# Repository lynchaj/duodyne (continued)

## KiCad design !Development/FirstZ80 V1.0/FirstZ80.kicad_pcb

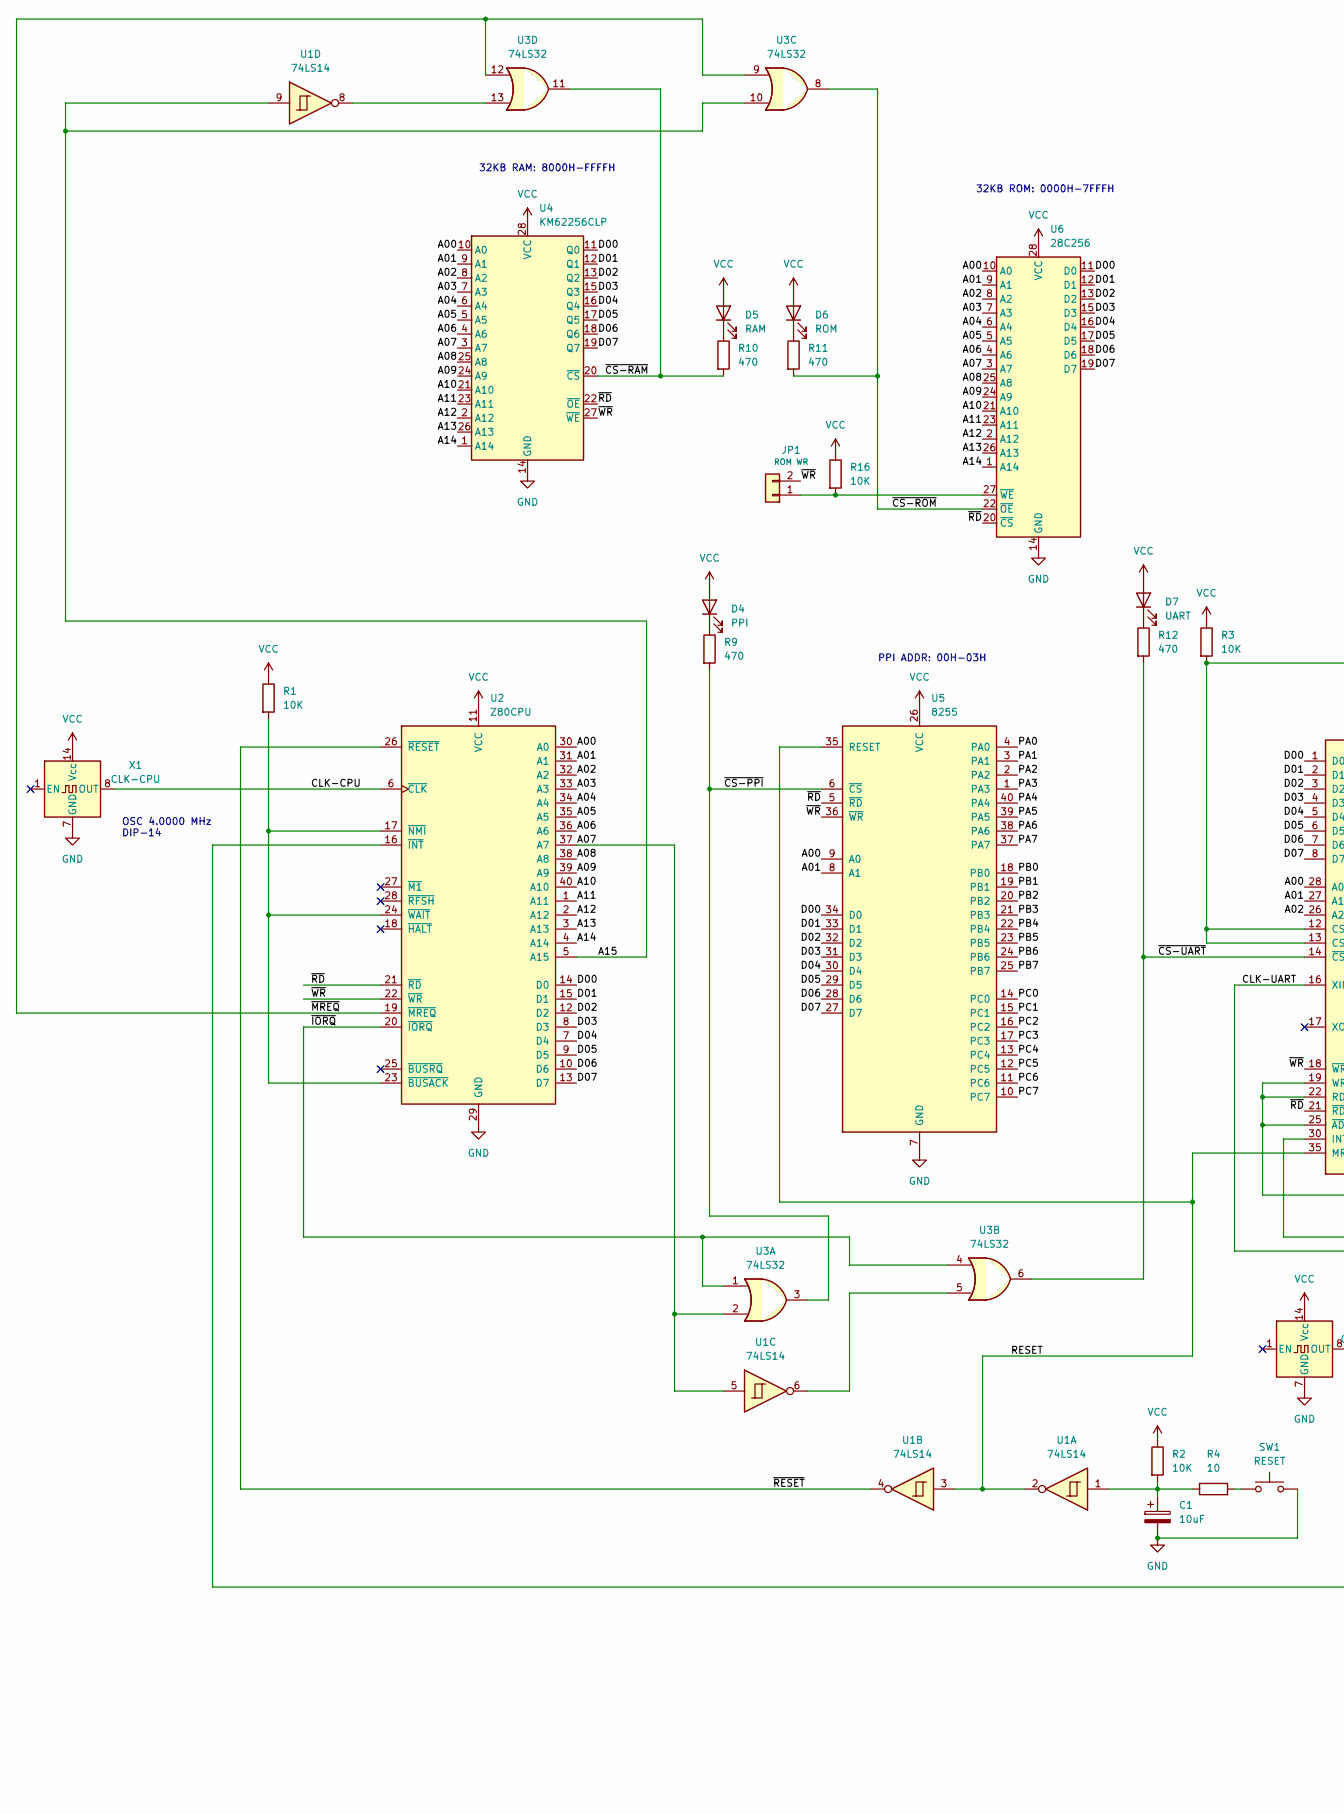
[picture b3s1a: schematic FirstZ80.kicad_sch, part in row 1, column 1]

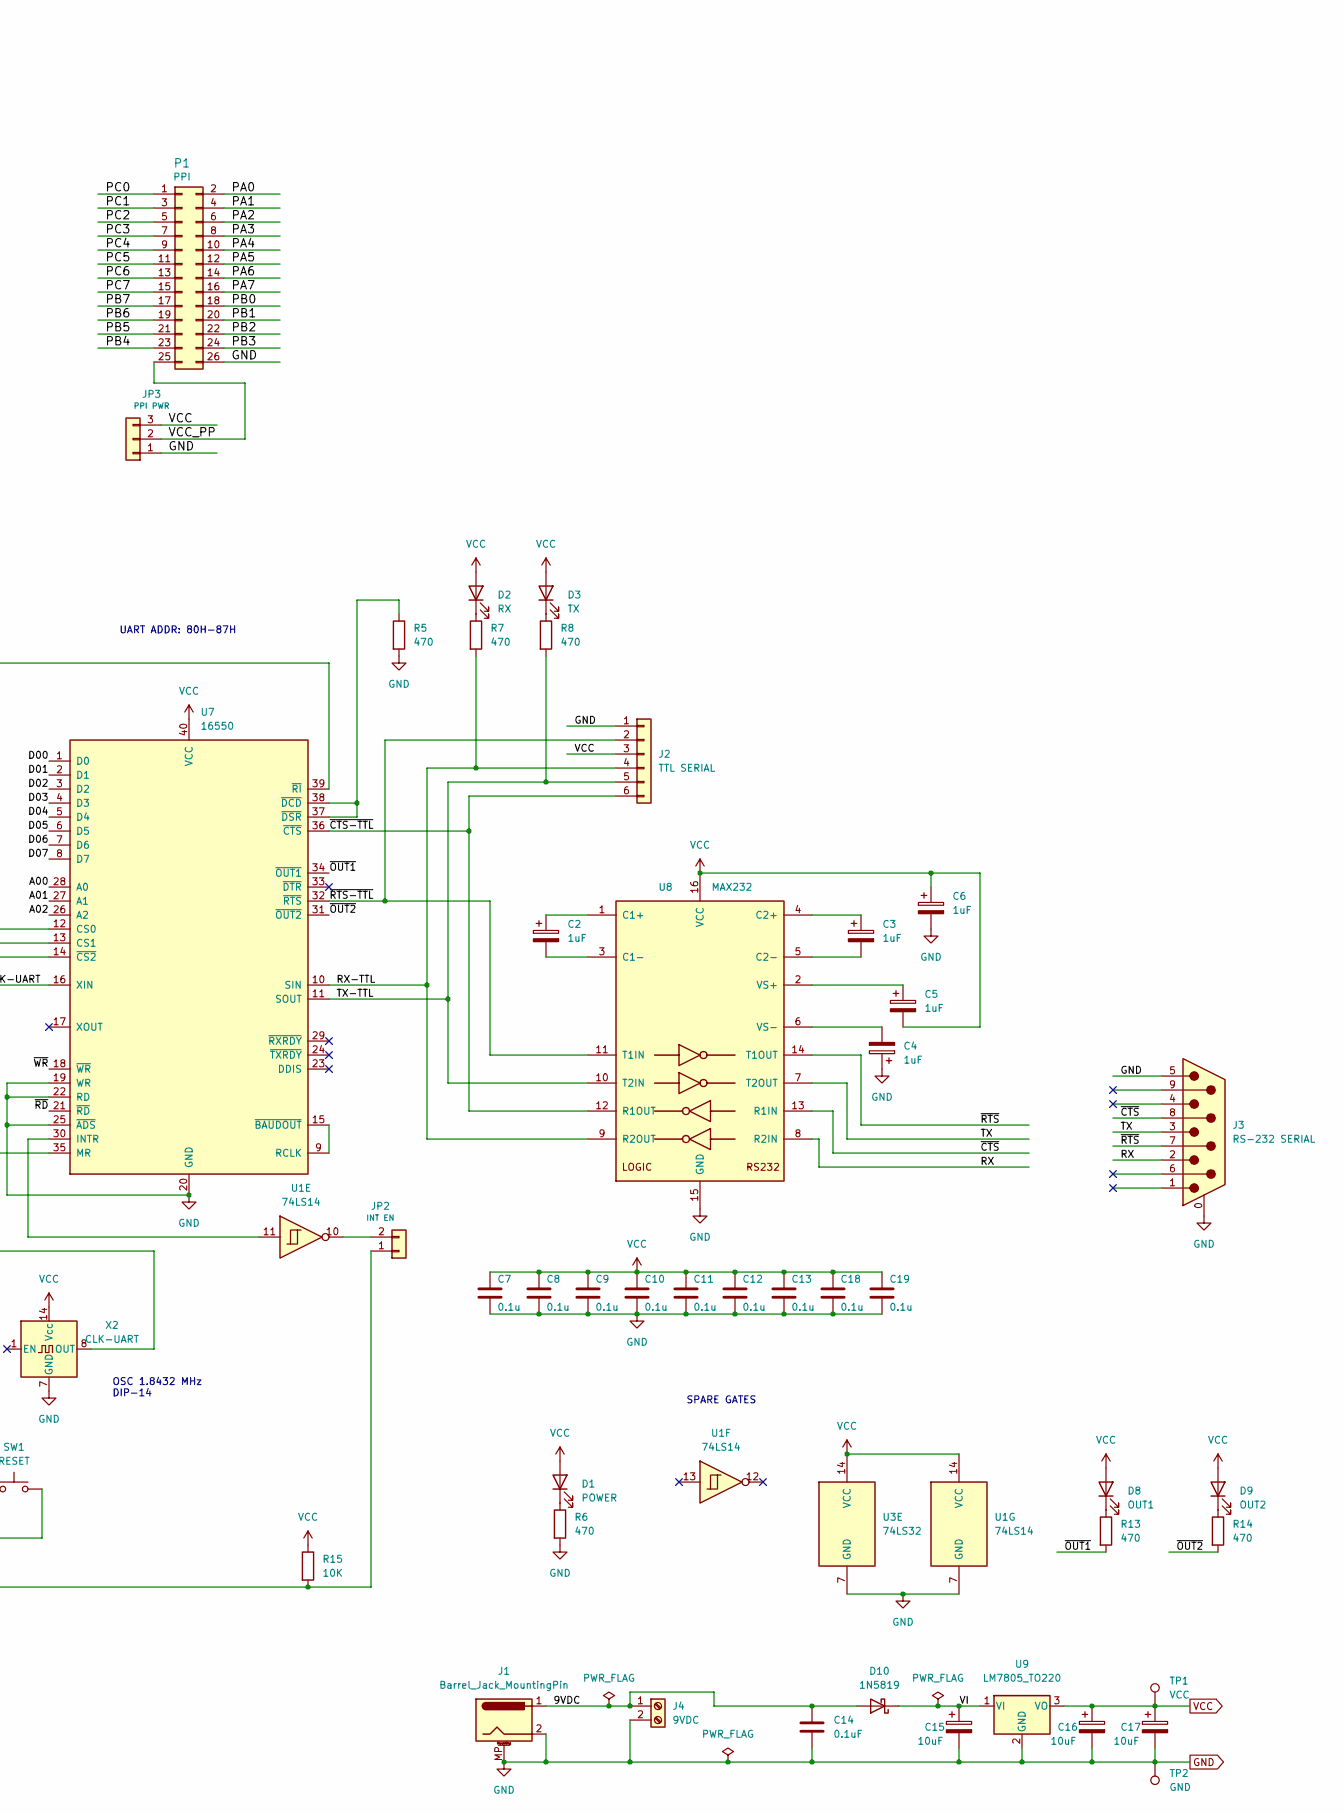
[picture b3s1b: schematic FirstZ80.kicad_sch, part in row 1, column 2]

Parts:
C1, C15, C16, C17: 10uF; CP_Radial_D5.0mm_P2.50mm
C2, C3, C4, C5, C6: 1uF; CP_Radial_D5.0mm_P2.50mm
C7, C8, C9, C10, C11, C12, C13, C18, C19: 0.1u; C_Disc_D5.0mm_W2.5mm_P5.00mm
C14: 0.1uF; C_Disc_D5.0mm_W2.5mm_P5.00mm
D1: POWER; LED_D3.0mm
D2: RX; LED_D3.0mm
D3: TX; LED_D3.0mm
D4: PPI; LED_D3.0mm
D5: RAM; LED_D3.0mm
D6: ROM; LED_D3.0mm
D7: UART; LED_D3.0mm
D8: OUT1; LED_D3.0mm
D9: OUT2; LED_D3.0mm
D10: 1N5819; D_DO-41_SOD81_P10.16mm_Horizontal
J1: Barrel_Jack_MountingPin; BarrelJack_Horizontal
J2: TTL SERIAL; PinHeader_1x06_P2.54mm_Horizontal
J3: RS-232 SERIAL; DSUB-9_Male_Horizontal_P2.77x2.84mm_EdgePinOffset4.94mm_Hou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
J4: 9VDC; TerminalBlock_Phoenix_MKDS-1,5-2-5.08_1x02_P5.08mm_Horizont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
JP1: ROM WR; PinHeader_1x02_P2.54mm_Vertical
JP2: INT EN; PinHeader_1x02_P2.54mm_Vertical
JP3: PPI PWR; PinHeader_1x03_P2.54mm_Vertical
P1: PPI; IDC-Header_2x13_P2.54mm_Horizontal
R1, R2, R3, R15, R16: 10K; R_Axial_DIN0207_L6.3mm_D2.5mm_P7.62mm_Horizontal
R4: 10; R_Axial_DIN0207_L6.3mm_D2.5mm_P7.62mm_Horizontal
R5, R6, R7, R8, R9, R10, R11, R12, R13, R14: 470; R_Axial_DIN0207_L6.3mm_D2.5mm_P7.62mm_Horizontal
SW1: RESET; SW_PUSH_6mm
TP1: VCC; PinHeader_1x01_P2.54mm_Vertical
TP2: GND; PinHeader_1x01_P2.54mm_Vertical
U1: 74LS14; DIP-14_W7.62mm_Socket_LongPads
U2: Z80CPU; DIP-40_W15.24mm_Socket_LongPads
U3: 74LS32; DIP-14_W7.62mm_Socket_LongPads
U4: KM62256CLP; DIP-28_W15.24mm_Socket_LongPads
U5: 8255; DIP-40_W15.24mm_Socket_LongPads
U6: 28C256; DIP_Socket-28_W11.9_W12.7_W15.24_W17.78_W18.5_3M_228-1277-0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
U7: 16550; DIP-40_W15.24mm_Socket_LongPads
U8: MAX232; DIP-16_W7.62mm_Socket_LongPads
U9: LM7805_TO220; TO-220-3_Horizontal_TabDown
X1: CLK-CPU; Oscillator_DIP-14
X2: CLK-UART; Oscillator_DIP-14

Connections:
/9VDC: C14.1, D10.2 (A), J1.1, J4.1
/A00: U2.30 (A0), U4.10 (A0), U5.9 (A0), U6.10 (A0), U7.28 (A0)
/A01: U2.31 (A1), U4.9 (A1), U5.8 (A1), U6.9 (A1), U7.27 (A1)
/A02: U2.32 (A2), U4.8 (A2), U6.8 (A2), U7.26 (A2)
/A03: U2.33 (A3), U4.7 (A3), U6.7 (A3)
/A04: U2.34 (A4), U4.6 (A4), U6.6 (A4)
/A05: U2.35 (A5), U4.5 (A5), U6.5 (A5)
/A06: U2.36 (A6), U4.4 (A6), U6.4 (A6)
/A07: U1.5, U2.37 (A7), U3.2, U4.3 (A7), U6.3 (A7)
/A08: U2.38 (A8), U4.25 (A8), U6.25 (A8)
/A09: U2.39 (A9), U4.24 (A9), U6.24 (A9)
/A10: U2.40 (A10), U4.21 (A10), U6.21 (A10)
/A11: U2.1 (A11), U4.23 (A11), U6.23 (A11)
/A12: U2.2 (A12), U4.2 (A12), U6.2 (A12)
/A13: U2.3 (A13), U4.26 (A13), U6.26 (A13)
/A14: U2.4 (A14), U4.1 (A14), U6.1 (A14)
/A15: U1.9, U2.5 (A15), U3.10
/CLK-CPU: U2.6 (~CLK), X1.8 (OUT)
/CLK-UART: U7.16 (XIN), X2.8 (OUT)
/D00: U2.14 (D0), U4.11 (Q0), U5.34 (D0), U6.11 (D0), U7.1 (D0)
/D01: U2.15 (D1), U4.12 (Q1), U5.33 (D1), U6.12 (D1), U7.2 (D1)
/D02: U2.12 (D2), U4.13 (Q2), U5.32 (D2), U6.13 (D2), U7.3 (D2)
/D03: U2.8 (D3), U4.15 (Q3), U5.31 (D3), U6.15 (D3), U7.4 (D3)
/D04: U2.7 (D4), U4.16 (Q4), U5.30 (D4), U6.16 (D4), U7.5 (D4)
/D05: U2.9 (D5), U4.17 (Q5), U5.29 (D5), U6.17 (D5), U7.6 (D5)
/D06: U2.10 (D6), U4.18 (Q6), U5.28 (D6), U6.18 (D6), U7.7 (D6)
/D07: U2.13 (D7), U4.19 (Q7), U5.27 (D7), U6.19 (D7), U7.8 (D7)
/PA0: P1.2, U5.4 (PA0)
/PA1: P1.4, U5.3 (PA1)
/PA2: P1.6, U5.2 (PA2)
/PA3: P1.8, U5.1 (PA3)
/PA4: P1.10, U5.40 (PA4)
/PA5: P1.12, U5.39 (PA5)
/PA6: P1.14, U5.38 (PA6)
/PA7: P1.16, U5.37 (PA7)
/PB0: P1.18, U5.18 (PB0)
/PB1: P1.20, U5.19 (PB1)
/PB2: P1.22, U5.20 (PB2)
/PB3: P1.24, U5.21 (PB3)
/PB4: P1.23, U5.22 (PB4)
/PB5: P1.21, U5.23 (PB5)
/PB6: P1.19, U5.24 (PB6)
/PB7: P1.17, U5.25 (PB7)
/PC0: P1.1, U5.14 (PC0)
/PC1: P1.3, U5.15 (PC1)
/PC2: P1.5, U5.16 (PC2)
/PC3: P1.7, U5.17 (PC3)
/PC4: P1.9, U5.13 (PC4)
/PC5: P1.11, U5.12 (PC5)
/PC6: P1.13, U5.11 (PC6)
/PC7: P1.15, U5.10 (PC7)
/RESET: U1.2, U1.3, U5.35 (RESET), U7.35 (MR)
/RX: J3.2, U8.8 (R2IN)
/RX-TTL: J2.4, R7.2, U7.10 (SIN), U8.9 (R2OUT)
/TX: J3.3, U8.7 (T2OUT)
/TX-TTL: J2.5, R8.2, U7.11 (SOUT), U8.10 (T2IN)
/VCC_PP: JP3.2, P1.25
/VI: C15.1, D10.1 (K), U9.1 (VI)
/~CS-PPI: R9.2, U3.3, U5.6 (~CS)
/~CS-RAM: R10.2, U3.11, U4.20 (~CS)
/~CS-ROM: R11.2, U3.8, U6.22 (~OE)
/~CS-UART: R12.2, U3.6, U7.14 (~CS2)
/~CTS-TTL: J2.6, U7.36 (~CTS), U8.12 (R1OUT)
/~CTS: J3.8, U8.13 (R1IN)
/~IORQ: U2.20 (~IORQ), U3.1, U3.4
/~MREQ: U2.19 (~MREQ), U3.9, U3.12
/~OUT1: R13.2, U7.34 (~OUT1)
/~OUT2: R14.2, U7.31 (~OUT2)
/~RD: U2.21 (~RD), U4.22 (~OE), U5.5 (~RD), U6.20 (~CS), U7.21 (~RD)
/~RESET: U1.4, U2.26 (~RESET)
/~RTS-TTL: J2.2, U7.32 (~RTS), U8.11 (T1IN)
/~RTS: J3.7, U8.14 (T1OUT)
/~WR: JP1.2, U2.22 (~WR), U4.27 (~WE), U5.36 (~WR), U7.18 (~WR)
GND: C1.2, C4.1, C6.2, C7.2, C8.2, C9.2, C10.2, C11.2, C12.2, C13.2, C14.2, C15.2, C16.2, C17.2, C18.2, C19.2, J1.2, J1.MP (MountPin), J2.1, J3.0 (PAD), J3.5, J4.2, JP3.1, P1.26, R5.2, R6.2, SW1.2, TP2.1, U1.7 (GND), U2.29 (GND), U3.7 (GND), U4.14 (GND), U5.7 (GND), U6.14 (GND), U7.19 (WR), U7.20 (GND), U7.22 (RD), U7.25 (~ADS), U8.15 (GND), U9.2 (GND), X1.7 (GND), X2.7 (GND)
unnamed: C1.1, R2.2, R4.1, U1.1
unnamed: C2.1, U8.1 (C1+)
unnamed: C2.2, U8.3 (C1-)
unnamed: C3.1, U8.4 (C2+)
unnamed: C3.2, U8.5 (C2-)
unnamed: C4.2, U8.6 (VS-)
unnamed: C5.1, U8.2 (VS+)
unnamed: D1.1 (K), R6.1
unnamed: D2.1 (K), R7.1
unnamed: D3.1 (K), R8.1
unnamed: D4.1 (K), R9.1
unnamed: D5.1 (K), R10.1
unnamed: D6.1 (K), R11.1
unnamed: D7.1 (K), R12.1
unnamed: D8.1 (K), R13.1
unnamed: D9.1 (K), R14.1
unnamed: JP1.1, R16.2, U6.27 (~WE)
unnamed: JP2.1, R15.2, U2.16 (~INT)
unnamed: JP2.2, U1.10
unnamed: R1.2, U2.17 (~NMI), U2.23 (~BUSACK), U2.24 (~WAIT)
unnamed: R3.2, U7.12 (CS0), U7.13 (CS1), U7.39 (~RI)
unnamed: R4.2, SW1.1
unnamed: R5.1, U7.37 (~DSR), U7.38 (~DCD)
unnamed: U1.6, U3.5
unnamed: U1.8, U3.13
unnamed: U1.11, U7.30 (INTR)
unnamed: U7.9 (RCLK), U7.15 (~BAUDOUT)
VCC: C5.2, C6.1, C7.1, C8.1, C9.1, C10.1, C11.1, C12.1, C13.1, C16.1, C17.1, C18.1, C19.1, D1.2 (A), D2.2 (A), D3.2 (A), D4.2 (A), D5.2 (A), D6.2 (A), D7.2 (A), D8.2 (A), D9.2 (A), J2.3, JP3.3, R1.1, R2.1, R3.1, R15.1, R16.1, TP1.1, U1.14 (VCC), U2.11 (VCC), U3.14 (VCC), U4.28 (VCC), U5.26 (VCC), U6.28 (VCC), U7.40 (VCC), U8.16 (VCC), U9.3 (VO), X1.14 (Vcc), X2.14 (Vcc)

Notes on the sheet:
UART ADDR: 80H-87H
SPARE GATES
PPI ADDR: 00H-03H
OSC 1.8432 MHz DIP-14
32KB ROM: 0000H-7FFFH
32KB RAM: 8000H-FFFFH
OSC 4.0000 MHz DIP-14

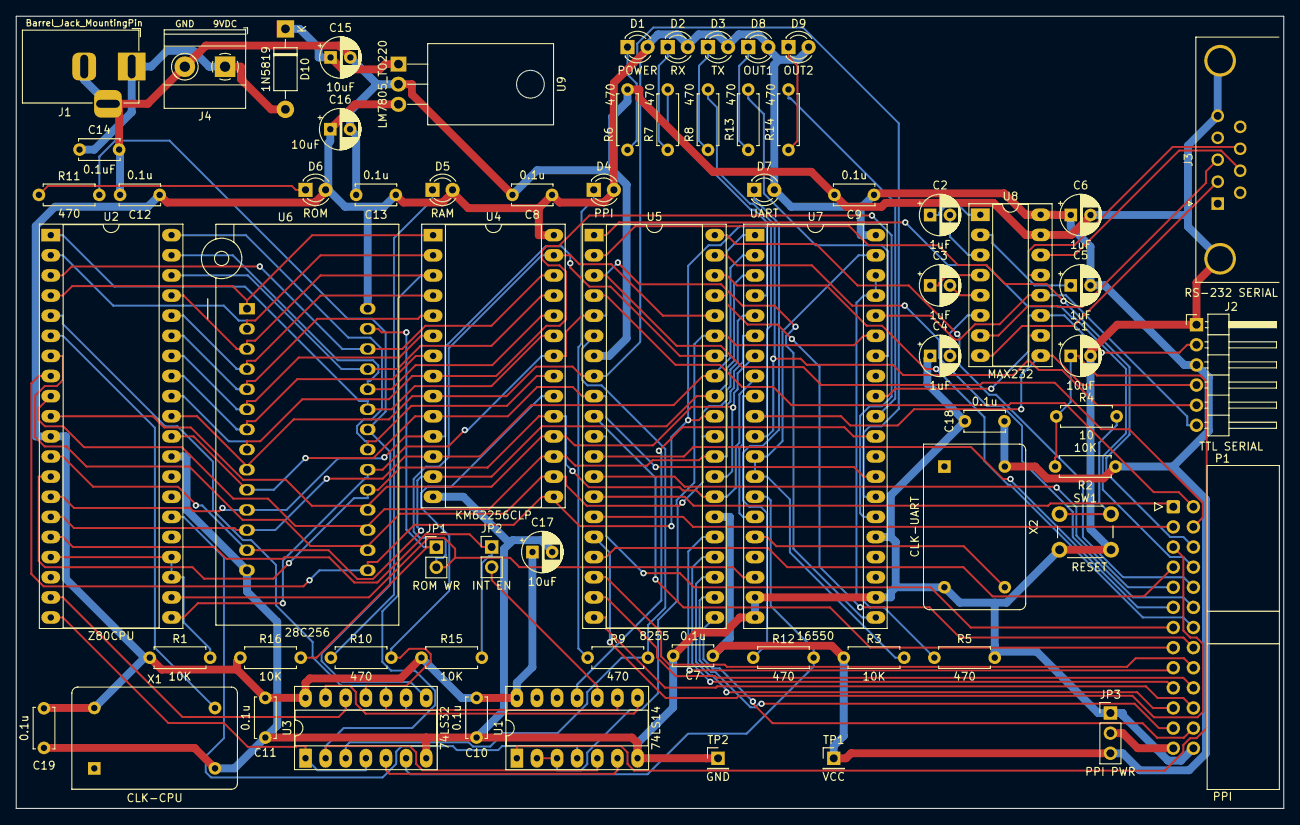
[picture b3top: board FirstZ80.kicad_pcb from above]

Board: 2 copper layers, 160.0 x 100.0 mm, 67 parts (0 on the bottom side), 102 nets.

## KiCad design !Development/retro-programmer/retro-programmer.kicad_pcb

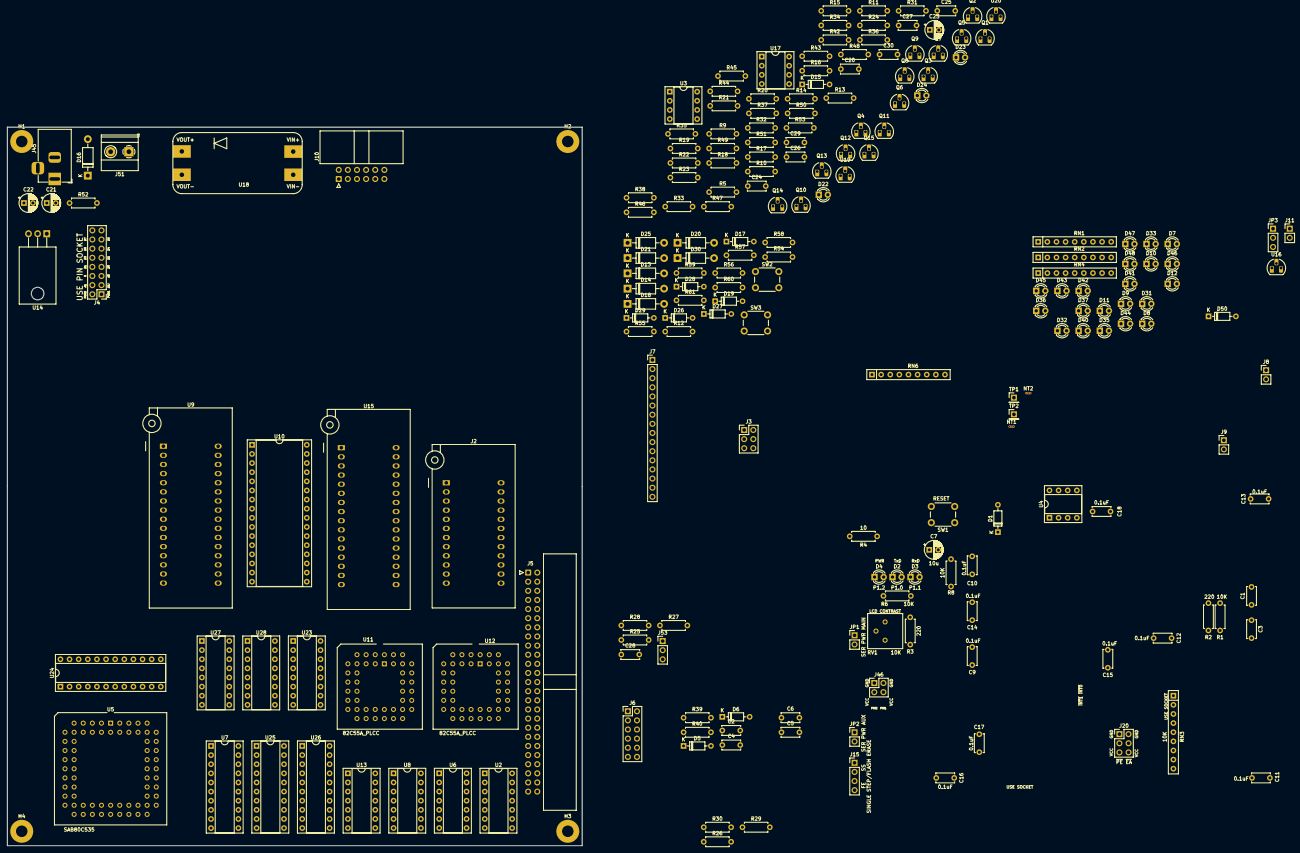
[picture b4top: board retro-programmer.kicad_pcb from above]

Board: 2 copper layers, 160.0 x 200.0 mm, 209 parts (0 on the bottom side), 228 nets, no tracks yet.

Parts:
C1, C2, C3, C4, C5, C6, C9, C10, C11, C12, C13, C14, C15, C16, C17, C18, C20, C24, C25, C26, C27, C28, C29, C30: 0.1uF; C_Disc_D5.0mm_W2.5mm_P5.00mm
C7: 10u; CP_Radial_D5.0mm_P2.50mm
C21, C22, C23: 10uF; CP_Radial_D5.0mm_P2.50mm
D1, D5, D6, D15, D17, D19, D26, D27, D28, D29, D50: 1N4148; D_DO-35_SOD27_P7.62mm_Horizontal
D2: P1.0; LED_D3.0mm
D3: P1.1; LED_D3.0mm
D4: P1.2; LED_D3.0mm
D7: P1.3; LED_D3.0mm
D8: P1.4; LED_D3.0mm
D9: P1.5; LED_D3.0mm
D10: P1.6; LED_D3.0mm
D11: P1.7; LED_D3.0mm
D12: ROM; LED_D3.0mm
D13, D14, D18, D20, D21, D25, D30: 1N4728A; D_DO-41_SOD81_P10.16mm_Horizontal
D16: 1N5819; D_DO-41_SOD81_P10.16mm_Horizontal
D22, D23: LED; LED_D3.0mm
D24: RAM; LED_D3.0mm
D31: PPI0; LED_D3.0mm
D32: PPI1; LED_D3.0mm
D33: LCD; LED_D3.0mm
D35: ~{OE}; LED_D3.0mm
D36: ~{WR}; LED_D3.0mm
D37: MMU; LED_D3.0mm
D40: FF; LED_D3.0mm
D41: T0; LED_D3.0mm
D42: T1; LED_D3.0mm
D43: ALE; LED_D3.0mm
D44: ~{IO-SEL}; LED_D3.0mm
D45: VCC; LED_D3.0mm
D46: TXD; LED_D3.0mm
D47: RXD; LED_D3.0mm
D48: ~{RES-OUT}; LED_D3.0mm
H1, H2, H3, H4: MountingHole_Pad; MountingHole_3.2mm_M3_Pad
J2: TTL/CMOS TESTER; DIP_Socket-24_W11.9_W12.7_W15.24_W17.78_W18.5_3M_224-1275-0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
J3: ADC INP; PinHeader_2x03_P2.54mm_Vertical
J4: LCD PORT; PinHeader_2x08_P2.54mm_Vertical
J5: EXP BUS; IDC-Header_2x25_P2.54mm_Horizontal
J6: PWR PINS; PinHeader_2x06_P2.54mm_Vertical
J7: ALT LCD PORT; PinHeader_1x16_P2.54mm_Vertical
J8: NMOS; PinHeader_1x02_P2.54mm_Vertical
J9: CMOS; PinHeader_1x02_P2.54mm_Vertical
J10: MAIN & AUX SERIAL; IDC-Header_2x06_P2.54mm_Horizontal
J11: EXT RES; PinHeader_1x02_P2.54mm_Vertical
J15: FE SS; PinHeader_1x04_P2.54mm_Vertical
J20: ~{PE} ~{EA}; PinHeader_2x03_P2.54mm_Vertical
J45: Barrel_Jack_MountingPin; BarrelJack_Horizontal
J46: LCD PWR; PinHeader_2x02_P2.54mm_Vertical
J51: 9VDC; TerminalBlock_Phoenix_MKDS-1,5-2-5.08_1x02_P5.08mm_Horizont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
J53: GND32; PinHeader_1x03_P2.54mm_Vertical
JP1: SER PWR MAIN; PinHeader_1x02_P2.54mm_Vertical
JP2: SER PWR AUX; PinHeader_1x02_P2.54mm_Vertical
JP3: RES SEL; PinHeader_1x03_P2.54mm_Vertical
NT1, NT2: NetTie_2; NetTie-2_THT_Pad0.3mm
Q1, Q4, Q5, Q8, Q9, Q12, Q13: 2N3904; TO-92_HandSolder
Q2, Q3, Q6, Q7, Q10, Q11, Q14, Q15: 2N3906; TO-92_HandSolder
R1, R6, R8, R10, R15, R16, R21, R22, R33, R34, R39, R40, R42, R50, R52, R53, R59, R60: 10K; R_Axial_DIN0207_L6.3mm_D2.5mm_P7.62mm_Horizontal
R2, R3: 220; R_Axial_DIN0207_L6.3mm_D2.5mm_P7.62mm_Horizontal
R4: 10; R_Axial_DIN0207_L6.3mm_D2.5mm_P7.62mm_Horizontal
R5, R9, R13, R14, R19, R20, R25, R26, R27, R28, R29, R30, R31, R32, R38: 4700; R_Axial_DIN0207_L6.3mm_D2.5mm_P7.62mm_Horizontal
R11, R17, R18, R23, R24, R35, R36, R48: 22K; R_Axial_DIN0207_L6.3mm_D2.5mm_P7.62mm_Horizontal
R12, R49, R54, R55, R56, R57, R58, R61: 2200; R_Axial_DIN0207_L6.3mm_D2.5mm_P7.62mm_Horizontal
R37: 1000; R_Axial_DIN0207_L6.3mm_D2.5mm_P7.62mm_Horizontal
R43: 100K; R_Axial_DIN0207_L6.3mm_D2.5mm_P7.62mm_Horizontal
R44: 39K; R_Axial_DIN0207_L6.3mm_D2.5mm_P7.62mm_Horizontal
R45: 5600; R_Axial_DIN0207_L6.3mm_D2.5mm_P7.62mm_Horizontal
R46, R47: 240; R_Axial_DIN0207_L6.3mm_D2.5mm_P7.62mm_Horizontal
R51: 8200; R_Axial_DIN0207_L6.3mm_D2.5mm_P7.62mm_Horizontal
RN1: 820; R_Array_SIP9
RN2, RN3, RN4: 10K; R_Array_SIP9
RN6: 470; R_Array_SIP9
RV1: 10K; Potentiometer_Bourns_3386P_Vertical
SW1: RESET; SW_PUSH_6mm
SW2: INPUT0; SW_PUSH_6mm
SW3: INPUT1; SW_PUSH_6mm
TP1: VCC; PinHeader_1x01_P2.54mm_Vertical
TP2: GND; PinHeader_1x01_P2.54mm_Vertical
U2: 74LS74; DIP-14_W7.62mm_Socket
U3, U4: X9C103PZ; DIP-8_W7.62mm_Socket
U5: SAB80C535; PLCC-68_THT-Socket
U6: 74LS14; DIP-14_W7.62mm_Socket
U7: 74LS373; DIP-20_W7.62mm_Socket
U8: 11.0592 MHz; DIP-14_W7.62mm_Socket
U9: SST39SF040; DIP_Socket-32_W11.9_W12.7_W15.24_W17.78_W18.5_3M_232-1285-0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
U10: AS6C4008-55PCN; DIP-32_W15.24mm_Socket
U11, U12: 82C55A_PLCC; PLCC-44_THT-Socket
U13: 74LS30; DIP-14_W7.62mm_Socket
U14: LM7805_TO220; TO-220-3_Horizontal_TabDown
U15: 27C080; DIP_Socket-32_W11.9_W12.7_W15.24_W17.78_W18.5_3M_232-1285-0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
U16: DS1233; TO-92L_HandSolder
U17: LM358; DIP-8_W7.62mm_Socket
U18: MT3608_module
U19, U20: LM317L_TO92; TO-92_HandSolder
U23: 74LS138; DIP-16_W7.62mm_Socket
U24: GAL22V10; DIP-24_W7.62mm_Socket
U25, U26: GAL16V8; DIP-20_W7.62mm_Socket
U27, U28: 74LS670; DIP-16_W7.62mm_Socket

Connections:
/GALS/CS-LCD-WR: U24.10 (I9), U24.22 (O1)
/MCU_SAB80C535/VBB: C1.1, J9.2, U5.37 (VCC)
/Power/9VDC: C20.1, D16.2 (A), J45.1, J51.1
A0: J4.5, J5.5, J7.5, U7.2 (O0), U9.12 (A0), U10.12 (A0), U11.10 (A0), U12.10 (A0), U27.14 (Wa), U28.14 (Wa)
A1: J4.4, J5.4, J7.4, U7.5 (O1), U9.11 (A1), U10.11 (A1), U11.9 (A1), U12.9 (A1), U26.6 (I6), U27.13 (Wb), U28.13 (Wb)
A2: J5.3, U7.6 (O2), U9.10 (A2), U10.10 (A2), U25.2 (I2), U26.5 (I5)
A3: J5.6, U7.9 (O3), U9.9 (A3), U10.9 (A3), U25.3 (I3), U26.4 (I4)
A4: J5.9, U7.12 (O4), U9.8 (A4), U10.8 (A4), U25.4 (I4), U26.3 (I3)
A5: J5.2, U7.15 (O5), U9.7 (A5), U10.7 (A5), U23.1 (A0)
A6: J5.7, U7.16 (O6), U9.6 (A6), U10.6 (A6), U23.2 (A1)
A7: J5.8, U7.19 (O7), U9.5 (A7), U10.5 (A7), U23.3 (A2)
A8: J5.10, U5.41 (P2.0), U9.27 (A8), U10.27 (A8), U13.12
A9: J5.14, U5.42 (P2.1), U9.26 (A9), U10.26 (A9), U13.11
A10: J5.12, U5.43 (P2.2), U9.23 (A10), U10.23 (A10), U13.6
A11: J5.23, U5.44 (P2.3), U9.25 (A11), U10.25 (A11), U13.5
A12: U5.45 (P2.4), U9.4 (A12), U10.4 (A12), U13.4
A13: U5.46 (P2.5), U9.28 (A13), U10.28 (A13), U13.3
A14: U5.47 (P2.6), U13.2, U27.5 (Ra), U28.5 (Ra)
A15: D12.1 (K), U5.48 (P2.7), U9.22 (CE), U13.1, U27.4 (Rb), U28.4 (Rb)
ALE: D43.1 (K), U5.50 (ALE), U7.11 (LE)
CLK: J5.11, U2.9 (Q), U5.39 (XTAL2)
D0: J4.7, J5.48, J7.7, RN3.2 (R1), U2.2 (D), U5.52 (P0.0), U7.3 (D0), U9.13 (D0), U10.13 (DQ0), U11.38 (D0), U12.38 (D0), U27.15 (D1)
D1: J4.8, J5.46, J7.8, RN3.3 (R2), U5.53 (P0.1), U7.4 (D1), U9.14 (D1), U10.14 (DQ1), U11.37 (D1), U12.37 (D1), U27.1 (D2)
D2: J4.9, J5.47, J7.9, RN3.4 (R3), U5.54 (P0.2), U7.7 (D2), U9.15 (D2), U10.15 (DQ2), U11.36 (D2), U12.36 (D2), U27.2 (D3)
D3: J4.10, J5.45, J7.10, RN3.5 (R4), U5.55 (P0.3), U7.8 (D3), U9.17 (D3), U10.17 (DQ3), U11.35 (D3), U12.35 (D3), U27.3 (D4)
D4: J4.11, J5.42, J7.11, RN3.6 (R5), U5.56 (P0.4), U7.13 (D4), U9.18 (D4), U10.18 (DQ4), U11.33 (D4), U12.33 (D4), U28.15 (D1)
D5: J4.12, J5.43, J7.12, RN3.7 (R6), U5.57 (P0.5), U7.14 (D5), U9.19 (D5), U10.19 (DQ5), U11.32 (D5), U12.32 (D5), U28.1 (D2)
D6: J4.13, J5.41, J7.13, RN3.8 (R7), U5.58 (P0.6), U7.17 (D6), U9.20 (D6), U10.20 (DQ6), U11.31 (D6), U12.31 (D6), U28.2 (D3)
D7: J4.14, J5.44, J7.14, RN3.9 (R8), U5.59 (P0.7), U7.18 (D7), U9.21 (D7), U10.21 (DQ7), U11.30 (D7), U12.30 (D7), U28.3 (D4)
E: J4.6, J7.6, U24.16 (O7)
GND: C1.2, C2.2, C3.2, C4.2, C5.2, C6.2, C7.2, C9.2, C10.2, C11.2, C12.2, C13.2, C14.2, C15.2, C16.2, C17.2, C18.2, C20.2, C21.2, C22.2, C23.2, C24.2, C25.2, C26.2, C27.2, C28.2, C29.2, C30.2, D13.2 (A), D14.2 (A), D18.2 (A), D20.2 (A), D21.2 (A), D22.1 (K), D23.1 (K), D25.2 (A), D30.2 (A), D45.1 (K), H1.1, H2.1, H3.1, H4.1, J4.16, J5.49, J5.50, J7.16, J8.1, J10.1, J10.2, J11.2, J15.2, J15.3, J20.1, J20.2, J45.2, J45.MP (MountPin), J46.2, J51.2, J53.3, NT1.1, Q1.1 (E), Q4.1 (E), Q5.1 (E), Q8.1 (E), Q9.1 (E), Q12.1 (E), Q13.1 (E), R25.2, R26.2, R27.2, R28.2, R29.2, R30.2, R42.2, R43.2, R49.2, R51.2, R53.2, RN6.1 (common), RV1.3, SW1.2, SW2.1, SW3.1, TP2.1, U2.7 (GND), U2.11 (C), U2.12 (D), U2.13 (~R), U3.4 (VSS), U3.6 (Vl/Rl), U4.4 (VSS), U4.6 (Vl/Rl), U5.12 (VAGND), U5.38 (GND), U6.7 (GND), U7.1 (OE), U7.10 (GND), U8.4, U8.7, U9.16 (GND), U10.16 (VSS), U11.8 (GND), U12.8 (GND), U13.7 (GND), U14.2 (GND), U16.1, U17.4 (V-), U18.2 (VIN-), U18.3 (VOUT-), U23.8 (GND), U24.12 (GND), U25.10 (GND), U26.10 (GND), U27.8 (GND), U28.8 (GND)
GND32: J53.2, U15.16 (GND)
INPUT0: U5.14 (P6.6), U6.2
INPUT1: U5.13 (P6.7), U6.4
LCD-ADJ: C3.1, J4.3, J7.3, RV1.2
LCD-PWR1: J4.1, J7.1, J46.4
LCD-PWR2: J4.2, J7.2, J46.1
unnamed: C2.1, D5.1 (K), R40.2, U6.1
unnamed: C4.1, D6.1 (K), R60.2, U6.3
unnamed: D1.2 (A), U5.7 (P4.5)
unnamed: D2.2 (A), RN1.9 (R8)
unnamed: D3.2 (A), RN1.8 (R7)
unnamed: D4.2 (A), RN1.7 (R6)
unnamed: D5.2 (A), R40.1, R59.2, SW2.2
unnamed: D6.2 (A), R39.2, R60.1, SW3.2
unnamed: D7.2 (A), RN1.6 (R5)
unnamed: D8.2 (A), RN1.5 (R4)
unnamed: D9.2 (A), RN1.4 (R3)
unnamed: D10.2 (A), RN1.3 (R2)
unnamed: D11.2 (A), RN1.2 (R1)
unnamed: D12.2 (A), RN2.2 (R1)
unnamed: D13.1 (K), R12.1, U5.15 (P6.5)
unnamed: D14.1 (K), J6.10, R54.1
unnamed: D15.2 (A), Q2.3 (C)
unnamed: D17.2 (A), U11.19 (PC3)
unnamed: D18.1 (K), J6.8, R55.1
unnamed: D19.2 (A), U11.17 (PC1)
unnamed: D20.1 (K), J6.2, R56.1
unnamed: D21.1 (K), J6.4, R57.1
unnamed: D22.2 (A), R37.2
unnamed: D23.2 (A), R38.2
unnamed: D24.2 (A), RN2.3 (R2)
unnamed: D25.1 (K), J6.6, R58.1
unnamed: D26.2 (A), U11.24 (PB3)
unnamed: D27.2 (A), U11.26 (PB5)
unnamed: D28.2 (A), U11.28 (PB7)
unnamed: D29.2 (A), U11.14 (PC5)
unnamed: D30.1 (K), J6.12, R61.1
unnamed: D31.2 (A), RN2.4 (R3)
unnamed: D32.2 (A), RN2.5 (R4)
unnamed: D33.2 (A), RN2.6 (R5)
unnamed: D35.2 (A), RN2.8 (R7)
unnamed: D36.2 (A), RN2.9 (R8)
unnamed: D37.2 (A), RN4.2 (R1)
unnamed: D40.2 (A), RN4.5 (R4)
unnamed: D41.2 (A), RN4.6 (R5)
unnamed: D42.2 (A), RN4.7 (R6)
unnamed: D43.2 (A), RN4.8 (R7)
unnamed: D44.2 (A), RN4.9 (R8)
unnamed: D45.2 (A), R1.1
unnamed: D46.2 (A), R2.1
unnamed: D47.2 (A), R3.1
unnamed: D48.2 (A), R6.1
unnamed: J3.2, U5.20 (P6.0)
unnamed: J3.4, U5.19 (P6.1)
unnamed: J3.6, U5.18 (P6.2)
unnamed: J6.1, U12.24 (PB3)
unnamed: J6.3, U12.26 (PB5)
unnamed: J6.5, U12.28 (PB7)
unnamed: J6.7, U12.17 (PC1)
unnamed: J6.9, U12.19 (PC3)
unnamed: J6.11, U12.14 (PC5)
unnamed: J10.5, JP1.2 (B)
unnamed: J10.6, JP2.2 (B)
unnamed: J11.1, JP3.3, R4.1, SW1.1
unnamed: Q1.2 (B), R5.2
unnamed: Q1.3 (C), R10.2
unnamed: Q2.2 (B), R9.2
unnamed: Q3.2 (B), R10.1, R11.1
unnamed: Q4.2 (B), R13.2
unnamed: Q4.3 (C), R15.2
unnamed: Q5.2 (B), R14.2
unnamed: Q5.3 (C), R16.2
unnamed: Q6.2 (B), R15.1, R17.1
unnamed: Q7.2 (B), R16.1, R18.1
unnamed: Q8.2 (B), R19.2
unnamed: Q8.3 (C), R21.2
unnamed: Q9.2 (B), R20.2
unnamed: Q9.3 (C), R22.2
unnamed: Q10.2 (B), R21.1, R23.1
unnamed: Q11.2 (B), R22.1, R24.1
unnamed: Q12.2 (B), R31.2
unnamed: Q12.3 (C), R33.2
unnamed: Q13.2 (B), R32.2
unnamed: Q13.3 (C), R34.2
unnamed: Q14.2 (B), R33.1, R35.1
unnamed: Q15.2 (B), R34.1, R36.1
unnamed: R42.1, R44.1, U17.2 (-)
unnamed: R43.1, R45.1, U17.6 (-)
unnamed: R44.2, R46.2, U17.1, U19.1 (ADJ)
unnamed: R45.2, R47.2, U17.7, U20.1 (ADJ)
unnamed: J8.2, U5.40 (XTAL1)
unnamed: U2.10 (~S), U8.8, U8.11
unnamed: U3.5 (Vw/Rw), U17.3 (+)
unnamed: U4.5 (Vw/Rw), U17.5 (+)
ONE: NT2.2, U2.4 (~S), U23.6 (E3)
P4.6: J5.34, U5.8 (P4.6)
P4.7: J5.36, U5.9 (P4.7)
RD-2716: R9.1, U5.63 (P5.4)
RESET: U11.39 (RESET), U12.39 (RESET), U24.15 (O8)
RX-LED: D47.1 (K), U24.17 (O6)
RxD: U5.21 (P3.0/RxD), U24.18 (O5)
RxD-0: J10.7, U24.9 (I8)
RxD-1: J10.8, U24.8 (I7)
T0: D41.1 (K), U5.25 (P3.4/T0), U24.7 (I6)
T1: D42.1 (K), J15.4, U5.26 (P3.5/T1)
TX-LED: D46.1 (K), U24.21 (O2)
TxD: U5.22 (P3.1/TxD), U24.6 (I5)
TxD-0: J10.9, U24.19 (O4)
TxD-1: J10.10, U24.20 (O3)
U/~D: U3.2 (U/~D), U4.2 (U/~D), U5.3 (P4.2)
VCC: C5.1, C6.1, C9.1, C10.1, C11.1, C12.1, C13.1, C14.1, C15.1, C16.1, C17.1, C18.1, C22.1, C23.1, C24.1, C25.1, C26.1, C27.1, D50.1 (K), J4.15, J5.1, J5.22, J7.15, J9.1, J20.5, J20.6, J46.3, JP1.1 (A), JP2.1 (A), NT2.1, R1.2, R2.2, R3.2, R6.2, R8.2, R39.1, R59.1, RN1.1 (common), RN2.1 (common), RN3.1 (common), RN4.1 (common), RV1.1, TP1.1, U2.14 (VCC), U3.3 (Vh/Rh), U3.8 (VCC), U4.3 (Vh/Rh), U4.8 (VCC), U5.11 (VAREF), U5.68 (VCC), U6.14 (VCC), U7.20 (VCC), U8.1, U8.14, U9.32 (VCC), U10.32 (VCC), U11.29 (VCC), U12.29 (VCC), U13.14 (VCC), U14.3 (VO), U16.3, U23.16 (VCC), U24.24 (VCC), U25.20 (VCC), U26.20 (VCC), U27.16 (VCC), U28.16 (VCC)
VCC-ADC: J3.3, R50.2, R51.1
VCC-DIP24: R13.1, U5.62 (P5.5)
VCC-DIP28: R19.1, U5.61 (P5.6)
VCC-DIP32: R31.1, U5.60 (P5.7)
VCC-OUT: C30.1, Q2.1 (E), Q6.1 (E), Q10.1 (E), Q14.1 (E), R17.2, R23.2, R35.2, R37.1, R47.1, R50.1, U20.2 (VO)
VIN: C21.1, D16.1 (K), R52.1, U14.1 (VI), U18.1 (VIN+), U20.3 (VI)
VIN-ADC: J3.1, R52.2, R53.1
VOUT: U17.8 (V+), U18.4 (VOUT+), U19.3 (VI)
VPP-2716: R5.1, U5.67 (P5.0)
VPP-2732: R14.1, U5.66 (P5.1)
VPP-ADC: J3.5, R48.2, R49.1
VPP-DIP28: R20.1, U5.65 (P5.2)
VPP-DIP32: R32.1, U5.64 (P5.3)
VPP-OUT: C29.1, Q3.1 (E), Q7.1 (E), Q11.1 (E), Q15.1 (E), R11.2, R18.2, R24.2, R36.2, R38.1, R46.1, R48.1, U19.2 (VO)
ZERO: NT1.2, U23.5 (E2)
mA14: J5.24, RN6.2 (R1), U9.29 (A14), U10.3 (A14), U27.10 (Q1)
mA15: J5.25, RN6.3 (R2), U9.3 (A15), U10.31 (A15), U27.9 (Q2)
mA16: J5.28, RN6.4 (R3), U9.2 (A16), U10.2 (A16), U27.7 (Q3)
mA17: J5.27, RN6.5 (R4), U9.30 (A17), U10.30 (A17), U27.6 (Q4)
mA18: J5.30, RN6.6 (R5), U9.1 (A18), U10.1 (A18), U28.10 (Q1)
mA19: J5.29, RN6.7 (R6), U25.7 (I7), U28.9 (Q2)
mA20: J5.32, RN6.8 (R7), U28.7 (Q3)
mA21: J5.31, RN6.9 (R8), U28.6 (Q4)
zA0: J2.1, U11.5 (PA0), U12.5 (PA0), U15.12 (A0)
zA1: J2.2, U11.4 (PA1), U12.4 (PA1), U15.11 (A1)
zA2: J2.3, U11.3 (PA2), U12.3 (PA2), U15.10 (A2)
zA3: J2.4, U11.2 (PA3), U12.2 (PA3), U15.9 (A3)
zA4: J2.5, U11.44 (PA4), U12.44 (PA4), U15.8 (A4)
zA5: J2.6, U11.43 (PA5), U12.43 (PA5), U15.7 (A5)
zA6: J2.7, U11.42 (PA6), U12.42 (PA6), U15.6 (A6)
zA7: J2.8, U11.41 (PA7), U12.41 (PA7), U15.5 (A7)
zA8: J2.9, U11.20 (PB0), U12.20 (PB0), U15.27 (A8)
zA9: J2.10, U11.21 (PB1), U12.21 (PB1), U15.26 (A9)
zA10: J2.11, U11.22 (PB2), U12.22 (PB2), U15.23 (A10)
zA11: D15.1 (K), D26.1 (K), J2.13, Q3.3 (C), R26.1, R56.2, U15.25 (A11)
zA12: J2.14, U11.25 (PB4), U12.25 (PB4), U15.4 (A12)
zA13: D27.1 (K), J2.15, Q6.3 (C), R27.1, R57.2, U15.28 (A13)
zA14: J2.16, U11.27 (PB6), U12.27 (PB6), U15.29 (A14)
zA15: D28.1 (K), J2.17, Q11.3 (C), R28.1, R58.2, U15.3 (A15)
zA16: J2.18, U11.16 (PC0), U12.16 (PC0), U15.2 (A16)
zA17: D19.1 (K), J2.19, Q10.3 (C), R29.1, R55.2, U15.30 (A17)
zA18: J2.20, U11.18 (PC2), U12.18 (PC2), U15.31 (A18)
zA19: D17.1 (K), J2.21, Q15.3 (C), R30.1, R54.2, U15.1 (A19)
zCE: U5.1 (P4.0), U5.16 (P6.4), U15.22 (~CE)
zD0: D2.1 (K), U5.36 (P1.0/~INT3/CC0), U15.13 (D0)
zD1: D3.1 (K), U5.35 (P1.1/INT4/CC1), U15.14 (D1)
zD2: D4.1 (K), U5.34 (P1.2/INT5/CC2), U15.15 (D2)
zD3: D7.1 (K), U5.33 (P1.3/INT6/CC3), U15.17 (D3)
zD4: D8.1 (K), U5.32 (P1.4/~INT2), U15.18 (D4)
zD5: D9.1 (K), U5.31 (P1.5/T2EX), U15.19 (D5)
zD6: D10.1 (K), U5.30 (P1.6/CLKOUT), U15.20 (D6)
zD7: D11.1 (K), U5.29 (P1.7/T2), U15.21 (D7)
zGND: J2.12, J53.1, U11.15 (PC4), U12.15 (PC4)
zOE: D1.1 (K), Q7.3 (C), R12.2, R25.1, U15.24 (~OE)
zSPARE0: J2.22, J5.37, U11.13 (PC6), U12.13 (PC6)
zSPARE1: J2.23, J5.39, U11.11 (PC7), U12.11 (PC7)
zVCC: C28.1, D29.1 (K), J2.24, Q14.3 (C), R61.2, U15.32 (VCC)
~CS-DP0: U3.7 (~CS), U5.5 (P4.3)
~CS-DP1: U4.7 (~CS), U5.6 (P4.4)
~CS-FF-WR: D40.1 (K), U2.3 (C), U26.16 (IO4)
~CS-LCD: D33.1 (K), U24.5 (I4), U25.17 (I03)
~CS-MMU-WR: D37.1 (K), U25.16 (IO4), U27.12 (~Ew), U28.12 (~Ew)
~CS-PPI0: D31.1 (K), U11.7 (~CS), U25.19 (IO1)
~CS-PPI1: D32.1 (K), U12.7 (~CS), U25.18 (IO2)
~CS-RAM: D24.1 (K), U10.22 (CE#), U25.15 (IO5)
~EA: J20.4, U5.51 (~EA)
~INC: U3.1 (~INC), U4.1 (~INC), U5.2 (P4.1)
~INT0: J5.33, U5.23 (P3.2/~INT0)
~INT1: J5.35, J15.1, U5.24 (P3.3/~INT1)
~IO-SEL: D44.1 (K), U13.8, U23.4 (E1), U25.6 (I6)
~OE: D35.1 (K), J5.26, U9.24 (OE), U10.24 (OE#), U11.6 (~RD), U12.6 (~RD), U24.23 (O0), U26.8 (I8)
~PAGE-EN: U2.6 (~Q), U27.11 (~Er), U28.11 (~Er)
~PE: J20.3, U5.4 (~PE)
~PSEN: U5.49 (~PSEN), U24.3 (I2)
~RD: U5.28 (P3.7/~RD), U24.2 (I1)
~RES-IN: J5.40, JP3.2
~RES-OUT: C7.1, D48.1 (K), D50.2 (A), J5.38, JP3.1, R4.2, R8.1, U2.1 (~R), U5.10 (~RESET), U16.2, U24.11 (I10)
~WR: D36.1 (K), J5.21, U5.27 (P3.6/~WR), U9.31 (PGM), U10.29 (WE#), U11.40 (~WR), U12.40 (~WR), U24.4 (I3), U25.8 (I8), U26.7 (I7)
~Y0: U23.15 (O0), U25.5 (I5), U26.2 (I2)
~Y1: J5.19, U23.14 (O1)
~Y2: J5.18, U23.13 (O2)
~Y3: J5.17, U23.12 (O3)
~Y4: J5.15, U23.11 (O4)
~Y5: J5.16, U23.10 (O5)
~Y6: J5.20, U23.9 (O6)
~Y7: J5.13, U23.7 (O7)
